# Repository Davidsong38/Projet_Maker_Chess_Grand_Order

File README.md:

# Projet-Maker--chiquier
Projet d'échiquier électronique

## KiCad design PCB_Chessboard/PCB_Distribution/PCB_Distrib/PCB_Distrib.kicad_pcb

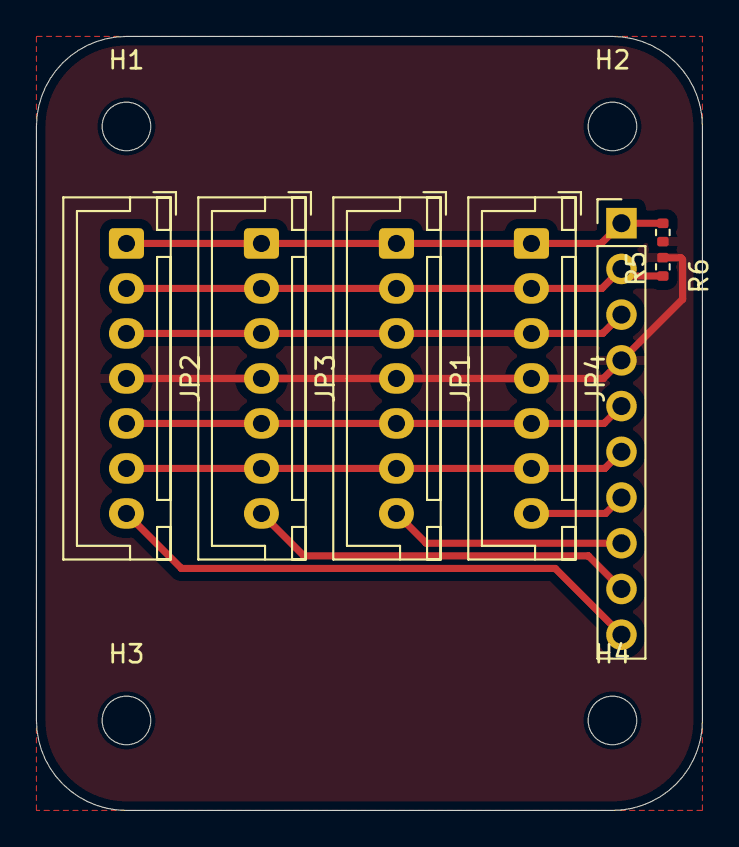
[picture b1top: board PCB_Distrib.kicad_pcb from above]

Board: 2 copper layers, 37.0 x 43.0 mm, 11 parts (0 on the bottom side), 10 nets.

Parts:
H1, H2, H3, H4: MountingHole_Pad; MountingHole_2.7mm
JP1, JP2, JP3, JP4: Conn_01x07_Socket; JST_XH_B7B-XH-A_1x07_P2.50mm_Vertical
JRasp1: Conn_01x10_Socket; PinHeader_1x10_P2.54mm_Vertical
R5, R6: 4.7k; R_0402_1005Metric

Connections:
+3.3V: JP1.4, JP2.4, JP3.4, JP4.4, JRasp1.4, R5.1, R6.1
+5V: JP1.5, JP2.5, JP3.5, JP4.5, JRasp1.5
GND: JP1.3, JP2.3, JP3.3, JP4.3, JRasp1.3
GPIO04: JP2.7, JRasp1.10
GPIO17: JP1.7, JRasp1.8
GPIO22: JP4.7, JRasp1.7
GPIO27: JP3.7, JRasp1.9
LED.DIN: JP1.6, JP2.6, JP3.6, JP4.6, JRasp1.6
SCL: JP1.2, JP2.2, JP3.2, JP4.2, JRasp1.2, R6.2
SDA: JP1.1, JP2.1, JP3.1, JP4.1, JRasp1.1, R5.2

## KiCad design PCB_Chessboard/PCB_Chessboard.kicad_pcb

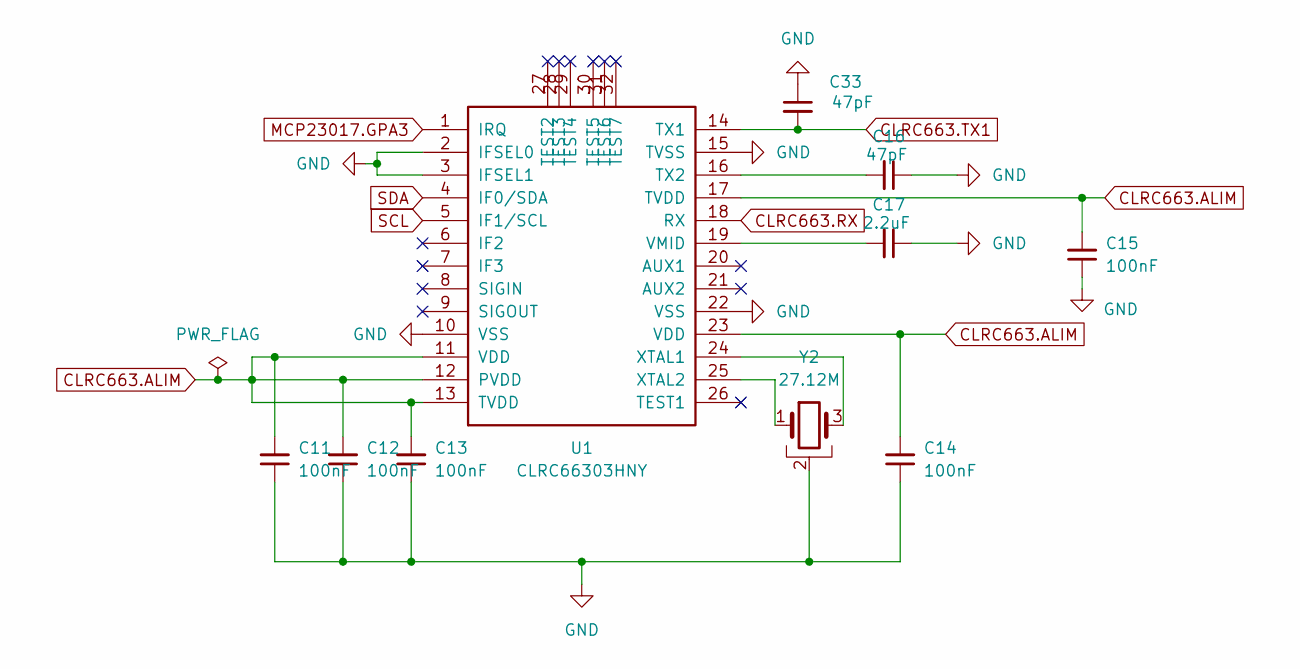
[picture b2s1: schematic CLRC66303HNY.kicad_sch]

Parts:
C11, C12, C13, C14, C15: 100nF; C_0402_1005Metric
C16, C33: 47pF; C_0402_1005Metric
C17: 2.2uF; C_0402_1005Metric
U1: CLRC66303HNY; HVQFN-32-1EP_5x5mm_P0.5mm_EP3.1x3.1mm
Y2: 27.12M; Crystal_SMD_2016-4Pin_2.0x1.6mm

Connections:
CLRC663.ALIM: C11.2, C12.2, C13.2, C14.2, C15.2, U1.11 (VDD), U1.12 (PVDD), U1.13 (TVDD), U1.17 (TVDD), U1.23 (VDD); also elsewhere on the board
CLRC663.RX: U1.18 (RX); also elsewhere on the board
CLRC663.TX1: C33.2, U1.14 (TX1); also elsewhere on the board
GND: C11.1, C12.1, C13.1, C14.1, C15.1, C16.1, C17.1, C33.1, U1.2 (IFSEL0), U1.3 (IFSEL1), U1.10 (VSS), U1.15 (TVSS), U1.22 (VSS), Y2.2; also elsewhere on the board
MCP23017.GPA3: U1.1 (IRQ); also elsewhere on the board
unnamed: C16.2, U1.16 (TX2)
unnamed: C17.2, U1.19 (VMID)
unnamed: U1.24 (XTAL1), Y2.3
unnamed: U1.25 (XTAL2), Y2.1
SCL: U1.5 (IF1/SCL); also elsewhere on the board
SDA: U1.4 (IF0/SDA); also elsewhere on the board

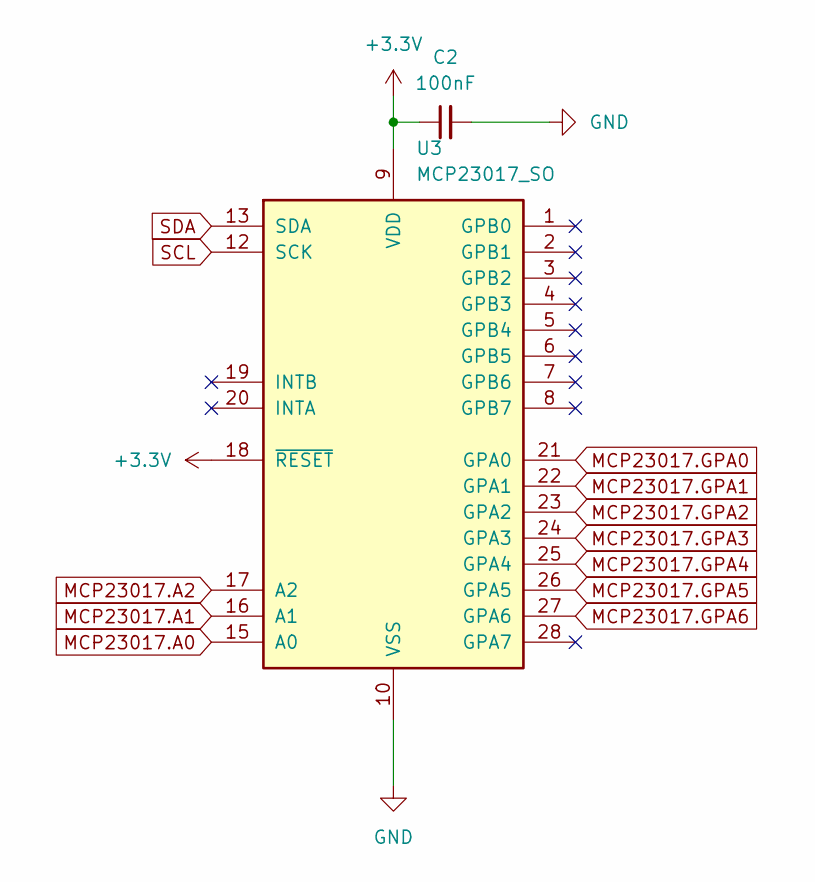
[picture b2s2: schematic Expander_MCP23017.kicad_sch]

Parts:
C2: 100nF; C_0402_1005Metric
U3: MCP23017_SO; SOIC-28W_7.5x17.9mm_P1.27mm

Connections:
+3.3V: C2.1, U3.9 (VDD), U3.18 (~RESET); also elsewhere on the board
GND: C2.2, U3.10 (VSS); also elsewhere on the board
MCP23017.A0: U3.15 (A0); also elsewhere on the board
MCP23017.A1: U3.16 (A1); also elsewhere on the board
MCP23017.A2: U3.17 (A2); also elsewhere on the board
MCP23017.GPA0: U3.21 (GPA0); also elsewhere on the board
MCP23017.GPA1: U3.22 (GPA1); also elsewhere on the board
MCP23017.GPA2: U3.23 (GPA2); also elsewhere on the board
MCP23017.GPA3: U3.24 (GPA3); also elsewhere on the board
MCP23017.GPA4: U3.25 (GPA4); also elsewhere on the board
MCP23017.GPA5: U3.26 (GPA5); also elsewhere on the board
MCP23017.GPA6: U3.27 (GPA6); also elsewhere on the board
SCL: U3.12 (SCK); also elsewhere on the board
SDA: U3.13 (SDA); also elsewhere on the board

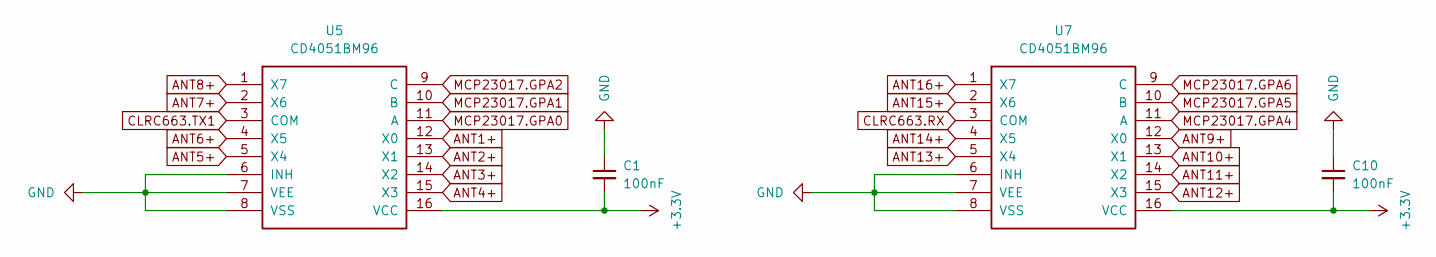
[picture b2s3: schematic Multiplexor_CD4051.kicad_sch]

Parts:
C1, C10: 100nF; C_0402_1005Metric
U5, U7: CD4051BM96; SOIC-16_3.9x9.9mm_P1.27mm

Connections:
+3.3V: C1.2, C10.2, U5.16 (VCC), U7.16 (VCC); also elsewhere on the board
ANT1+: U5.12 (X0); also elsewhere on the board
ANT2+: U5.13 (X1); also elsewhere on the board
ANT3+: U5.14 (X2); also elsewhere on the board
ANT4+: U5.15 (X3); also elsewhere on the board
ANT5+: U5.5 (X4); also elsewhere on the board
ANT6+: U5.4 (X5); also elsewhere on the board
ANT7+: U5.2 (X6); also elsewhere on the board
ANT8+: U5.1 (X7); also elsewhere on the board
ANT9+: U7.12 (X0); also elsewhere on the board
ANT10+: U7.13 (X1); also elsewhere on the board
ANT11+: U7.14 (X2); also elsewhere on the board
ANT12+: U7.15 (X3); also elsewhere on the board
ANT13+: U7.5 (X4); also elsewhere on the board
ANT14+: U7.4 (X5); also elsewhere on the board
ANT15+: U7.2 (X6); also elsewhere on the board
ANT16+: U7.1 (X7); also elsewhere on the board
CLRC663.RX: U7.3 (COM); also elsewhere on the board
CLRC663.TX1: U5.3 (COM); also elsewhere on the board
GND: C1.1, C10.1, U5.6 (INH), U5.7 (VEE), U5.8 (VSS), U7.6 (INH), U7.7 (VEE), U7.8 (VSS); also elsewhere on the board
MCP23017.GPA0: U5.11 (A); also elsewhere on the board
MCP23017.GPA1: U5.10 (B); also elsewhere on the board
MCP23017.GPA2: U5.9 (C); also elsewhere on the board
MCP23017.GPA4: U7.11 (A); also elsewhere on the board
MCP23017.GPA5: U7.10 (B); also elsewhere on the board
MCP23017.GPA6: U7.9 (C); also elsewhere on the board

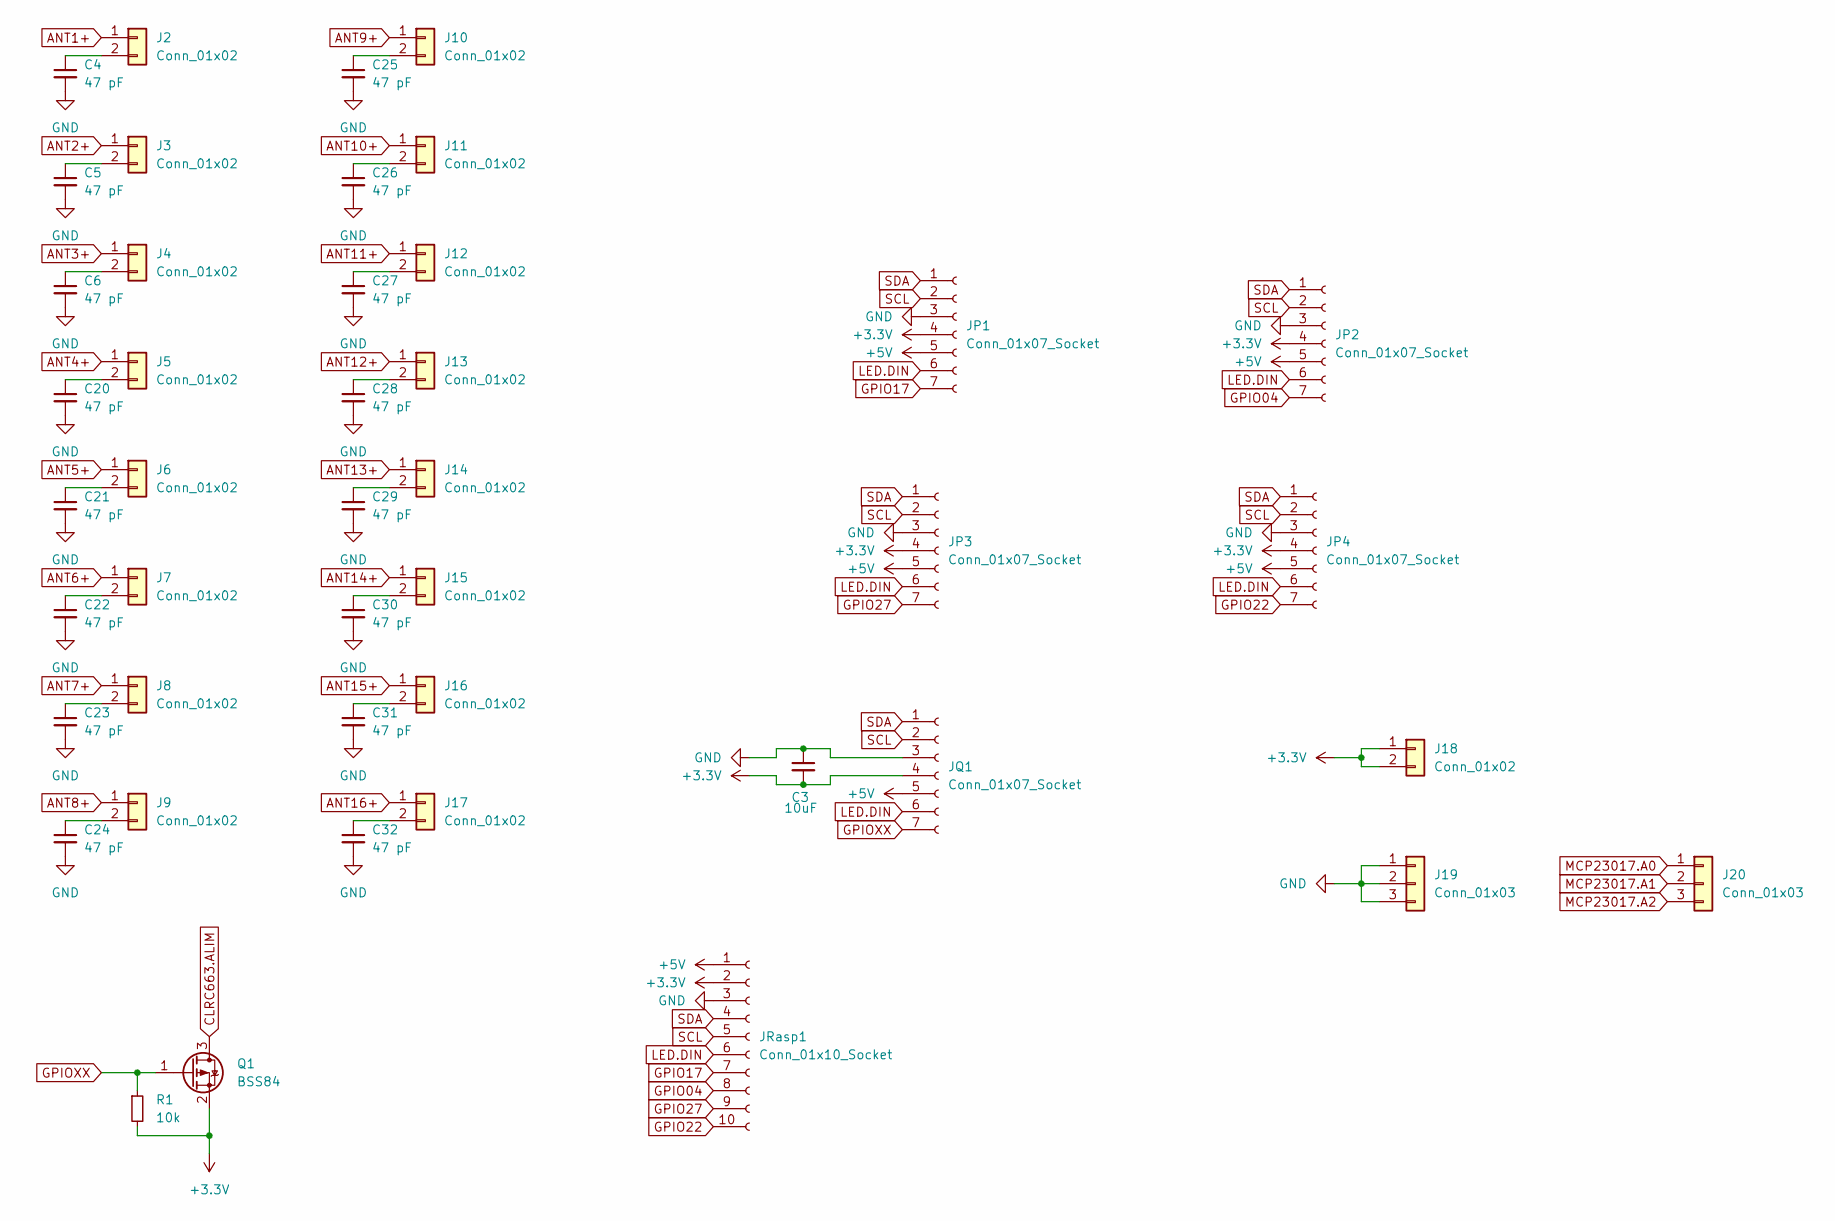
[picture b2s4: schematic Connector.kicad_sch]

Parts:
C3: 10uF; C_0402_1005Metric
C4, C5, C6, C20, C21, C22, C23, C24, C25, C26, C27, C28, C29, C30, C31, C32: 47 pF; C_0402_1005Metric
J2, J3, J4, J5, J6, J7, J8, J9, J10, J11, J12, J13, J14, J15, J16, J17, J18: Conn_01x02; PinHeader_1x02_P2.54mm_Vertical
J19, J20: Conn_01x03; PinHeader_1x03_P2.54mm_Vertical
JP1, JP2, JP3, JP4: Conn_01x07_Socket; JST_VH_B7PS-VH_1x07_P3.96mm_Horizontal
JQ1: Conn_01x07_Socket; JST_VH_B7PS-VH_1x07_P3.96mm_Horizontal
JRasp1: Conn_01x10_Socket; PinHeader_1x10_P1.00mm_Vertical
Q1: BSS84; SOT-23
R1: 10k; R_0402_1005Metric

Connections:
+3.3V: C3.2, J18.1, J18.2, JP1.4, JP2.4, JP3.4, JP4.4, JQ1.4, JRasp1.2, Q1.2 (S), R1.2; also elsewhere on the board
+5V: JP1.5, JP2.5, JP3.5, JP4.5, JQ1.5, JRasp1.1; also elsewhere on the board
ANT1+: J2.1; also elsewhere on the board
ANT2+: J3.1; also elsewhere on the board
ANT3+: J4.1; also elsewhere on the board
ANT4+: J5.1; also elsewhere on the board
ANT5+: J6.1; also elsewhere on the board
ANT6+: J7.1; also elsewhere on the board
ANT7+: J8.1; also elsewhere on the board
ANT8+: J9.1; also elsewhere on the board
ANT9+: J10.1; also elsewhere on the board
ANT10+: J11.1; also elsewhere on the board
ANT11+: J12.1; also elsewhere on the board
ANT12+: J13.1; also elsewhere on the board
ANT13+: J14.1; also elsewhere on the board
ANT14+: J15.1; also elsewhere on the board
ANT15+: J16.1; also elsewhere on the board
ANT16+: J17.1; also elsewhere on the board
CLRC663.ALIM: Q1.3 (D); also elsewhere on the board
GND: C3.1, C4.2, C5.2, C6.2, C20.2, C21.2, C22.2, C23.2, C24.2, C25.2, C26.2, C27.2, C28.2, C29.2, C30.2, C31.2, C32.2, J19.1, J19.2, J19.3, JP1.3, JP2.3, JP3.3, JP4.3, JQ1.3, JRasp1.3; also elsewhere on the board
GPIOXX: JQ1.7, Q1.1 (G), R1.1
LED.DIN: JP1.6, JP2.6, JP3.6, JP4.6, JQ1.6, JRasp1.6; also elsewhere on the board
MCP23017.A0: J20.1; also elsewhere on the board
MCP23017.A1: J20.2; also elsewhere on the board
MCP23017.A2: J20.3; also elsewhere on the board
unnamed: C4.1, J2.2
unnamed: C5.1, J3.2
unnamed: C6.1, J4.2
unnamed: C20.1, J5.2
unnamed: C21.1, J6.2
unnamed: C22.1, J7.2
unnamed: C23.1, J8.2
unnamed: C24.1, J9.2
unnamed: C25.1, J10.2
unnamed: C26.1, J11.2
unnamed: C27.1, J12.2
unnamed: C28.1, J13.2
unnamed: C29.1, J14.2
unnamed: C30.1, J15.2
unnamed: C31.1, J16.2
unnamed: C32.1, J17.2
unnamed: JP1.7, JRasp1.7
unnamed: JP2.7, JRasp1.8
unnamed: JP3.7, JRasp1.9
unnamed: JP4.7, JRasp1.10
SCL: JP1.2, JP2.2, JP3.2, JP4.2, JQ1.2, JRasp1.5; also elsewhere on the board
SDA: JP1.1, JP2.1, JP3.1, JP4.1, JQ1.1, JRasp1.4; also elsewhere on the board

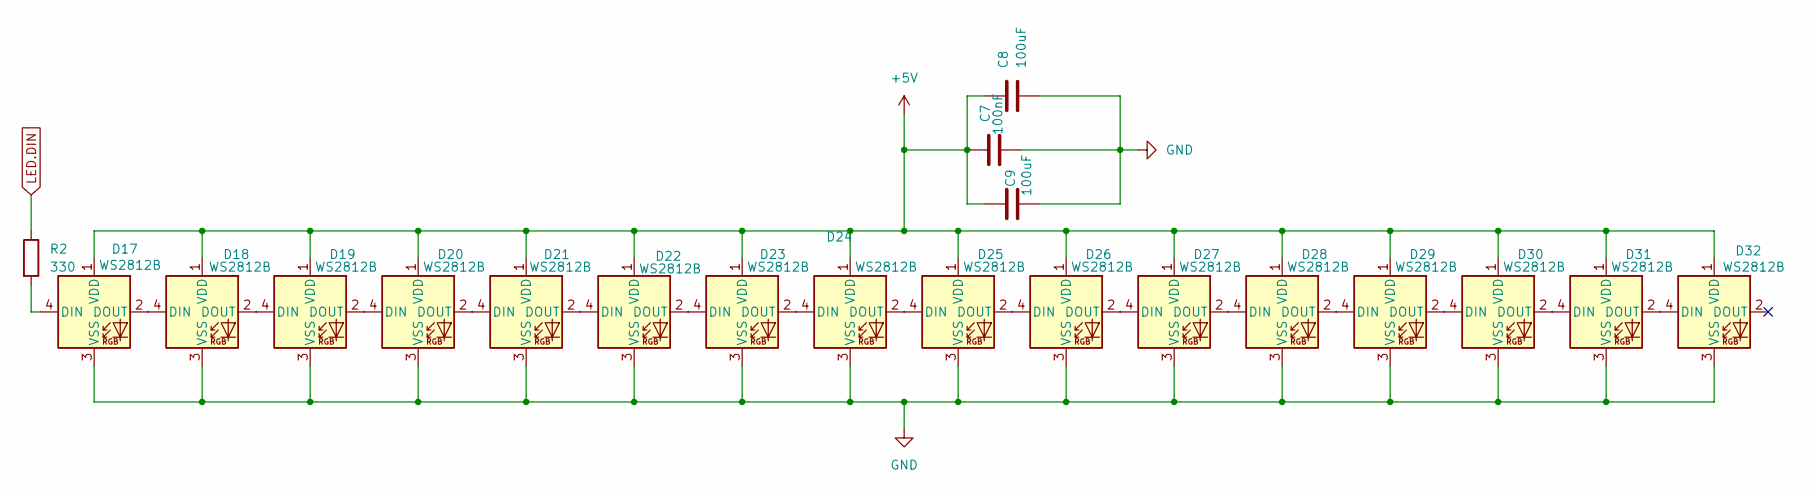
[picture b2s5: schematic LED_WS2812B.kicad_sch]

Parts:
C7: 100nF; C_0402_1005Metric
C8, C9: 100uF; C_0402_1005Metric
D17, D18, D19, D20, D21, D22, D23, D24, D25, D26, D27, D28, D29, D30, D31, D32: WS2812B; LED_WS2812B_PLCC4_5.0x5.0mm_P3.2mm
R2: 330; R_0402_1005Metric

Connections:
+5V: C7.1, C8.1, C9.1, D17.1 (VDD), D18.1 (VDD), D19.1 (VDD), D20.1 (VDD), D21.1 (VDD), D22.1 (VDD), D23.1 (VDD), D24.1 (VDD), D25.1 (VDD), D26.1 (VDD), D27.1 (VDD), D28.1 (VDD), D29.1 (VDD), D30.1 (VDD), D31.1 (VDD), D32.1 (VDD); also elsewhere on the board
GND: C7.2, C8.2, C9.2, D17.3 (VSS), D18.3 (VSS), D19.3 (VSS), D20.3 (VSS), D21.3 (VSS), D22.3 (VSS), D23.3 (VSS), D24.3 (VSS), D25.3 (VSS), D26.3 (VSS), D27.3 (VSS), D28.3 (VSS), D29.3 (VSS), D30.3 (VSS), D31.3 (VSS), D32.3 (VSS); also elsewhere on the board
LED.DIN: R2.1; also elsewhere on the board
unnamed: D17.4 (DIN), R2.2
unnamed: D17.2 (DOUT), D18.4 (DIN)
unnamed: D18.2 (DOUT), D19.4 (DIN)
unnamed: D19.2 (DOUT), D20.4 (DIN)
unnamed: D20.2 (DOUT), D21.4 (DIN)
unnamed: D21.2 (DOUT), D22.4 (DIN)
unnamed: D22.2 (DOUT), D23.4 (DIN)
unnamed: D23.2 (DOUT), D24.4 (DIN)
unnamed: D24.2 (DOUT), D25.4 (DIN)
unnamed: D25.2 (DOUT), D26.4 (DIN)
unnamed: D26.2 (DOUT), D27.4 (DIN)
unnamed: D27.2 (DOUT), D28.4 (DIN)
unnamed: D28.2 (DOUT), D29.4 (DIN)
unnamed: D29.2 (DOUT), D30.4 (DIN)
unnamed: D30.2 (DOUT), D31.4 (DIN)
unnamed: D31.2 (DOUT), D32.4 (DIN)

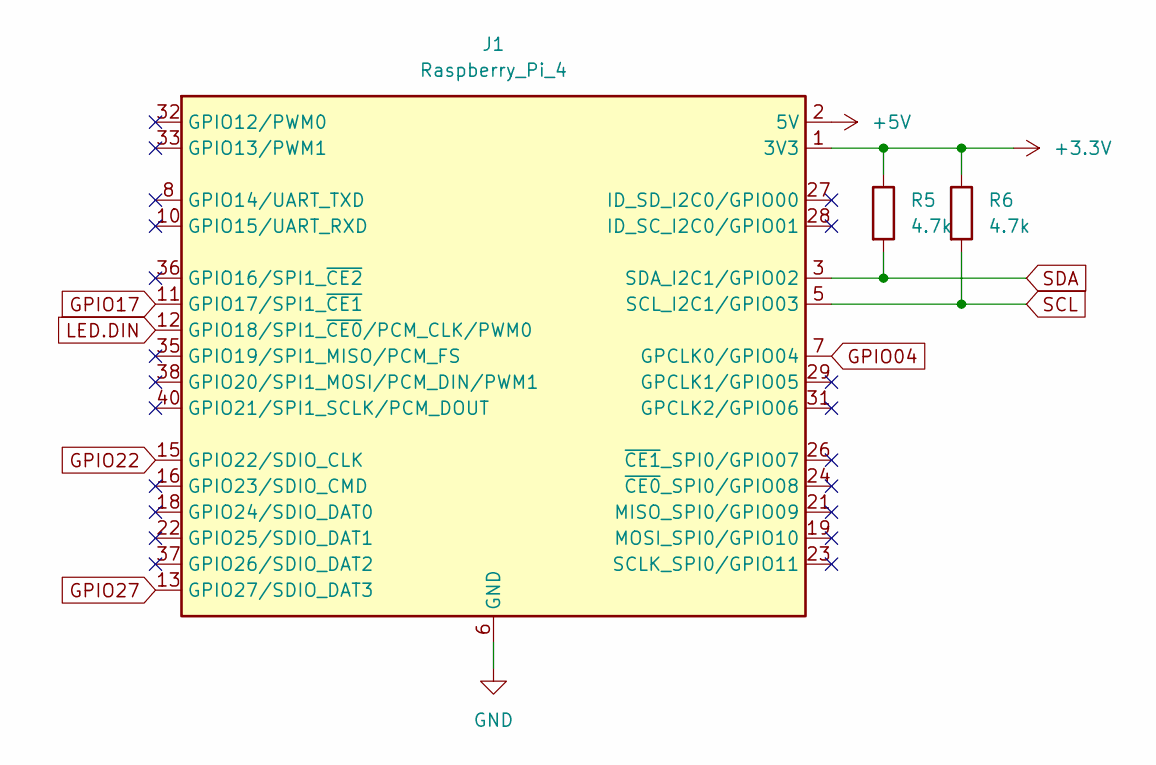
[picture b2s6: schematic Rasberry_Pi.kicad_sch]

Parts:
J1: Raspberry_Pi_4
R5, R6: 4.7k; R_0402_1005Metric

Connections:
unnamed: J1.1 (3V3), J1.17 (3V3), R5.1, R6.1
unnamed: J1.2 (5V), J1.4 (5V)
unnamed: J1.3 (SDA_I2C1/GPIO02), R5.2
unnamed: J1.5 (SCL_I2C1/GPIO03), R6.2
unnamed: J1.6 (GND), J1.9 (GND), J1.14 (GND), J1.20 (GND), J1.25 (GND), J1.30 (GND), J1.34 (GND), J1.39 (GND)

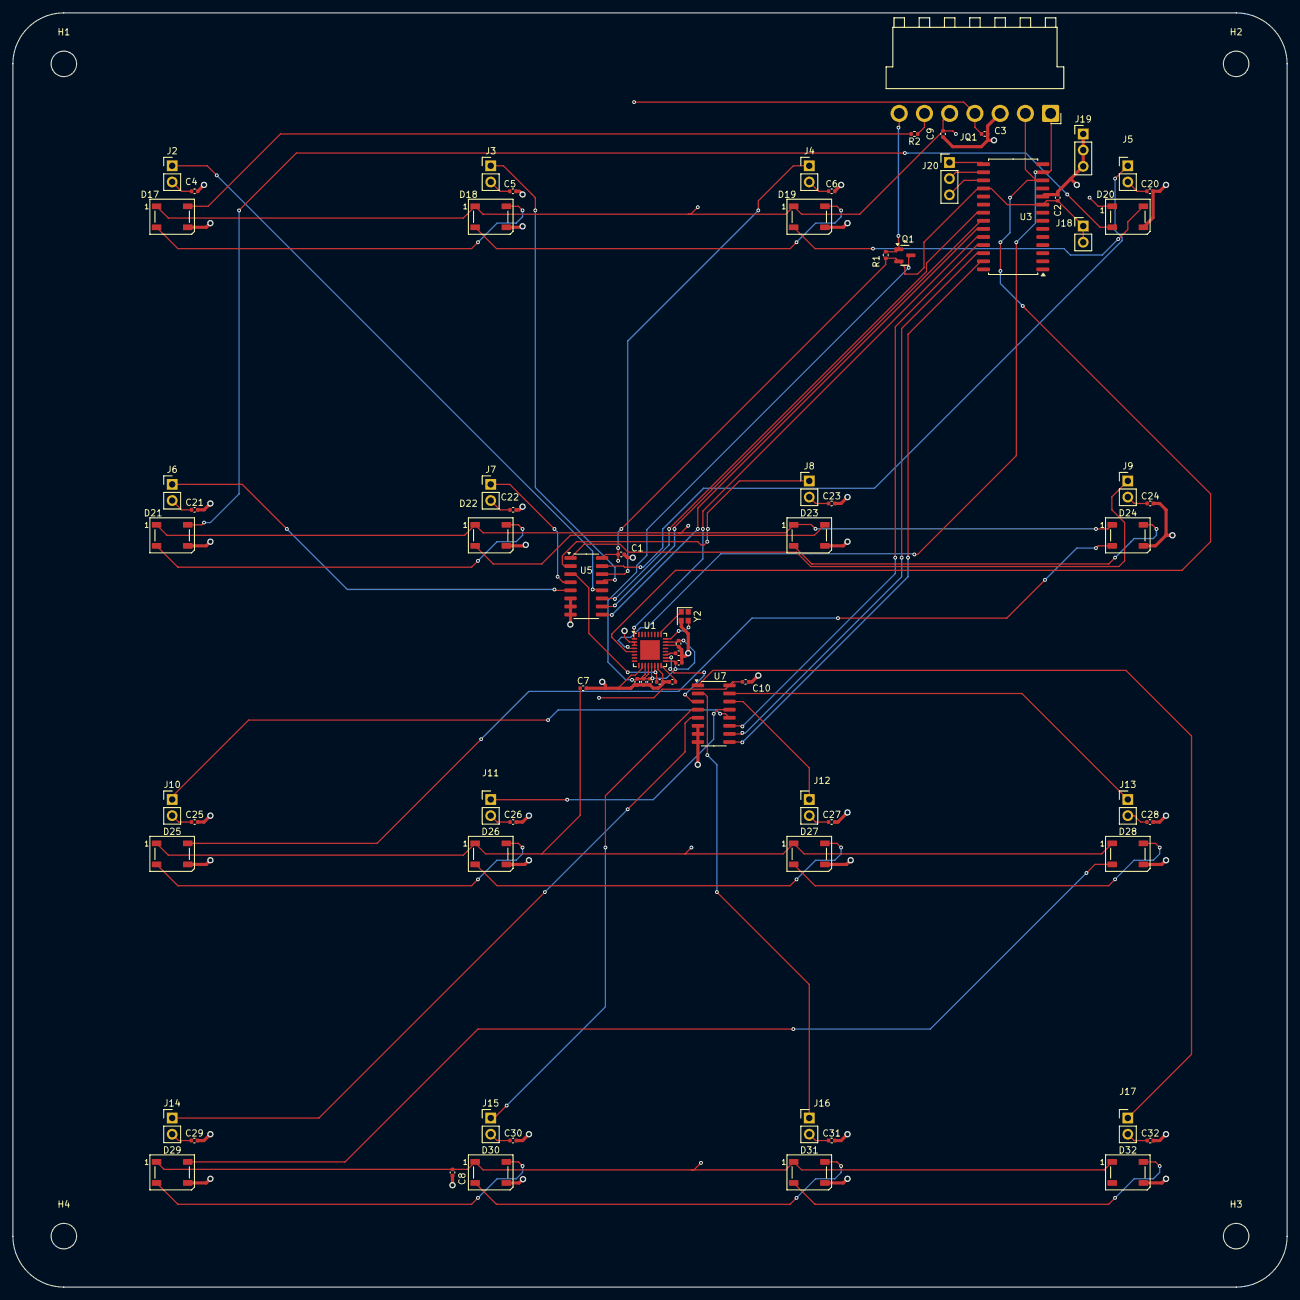
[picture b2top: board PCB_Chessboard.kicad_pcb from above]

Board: 4 copper layers, 200.0 x 200.0 mm, 79 parts (0 on the bottom side), 72 nets.

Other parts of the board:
H1, H2, H3, H4: MountingHole; MountingHole_4mm

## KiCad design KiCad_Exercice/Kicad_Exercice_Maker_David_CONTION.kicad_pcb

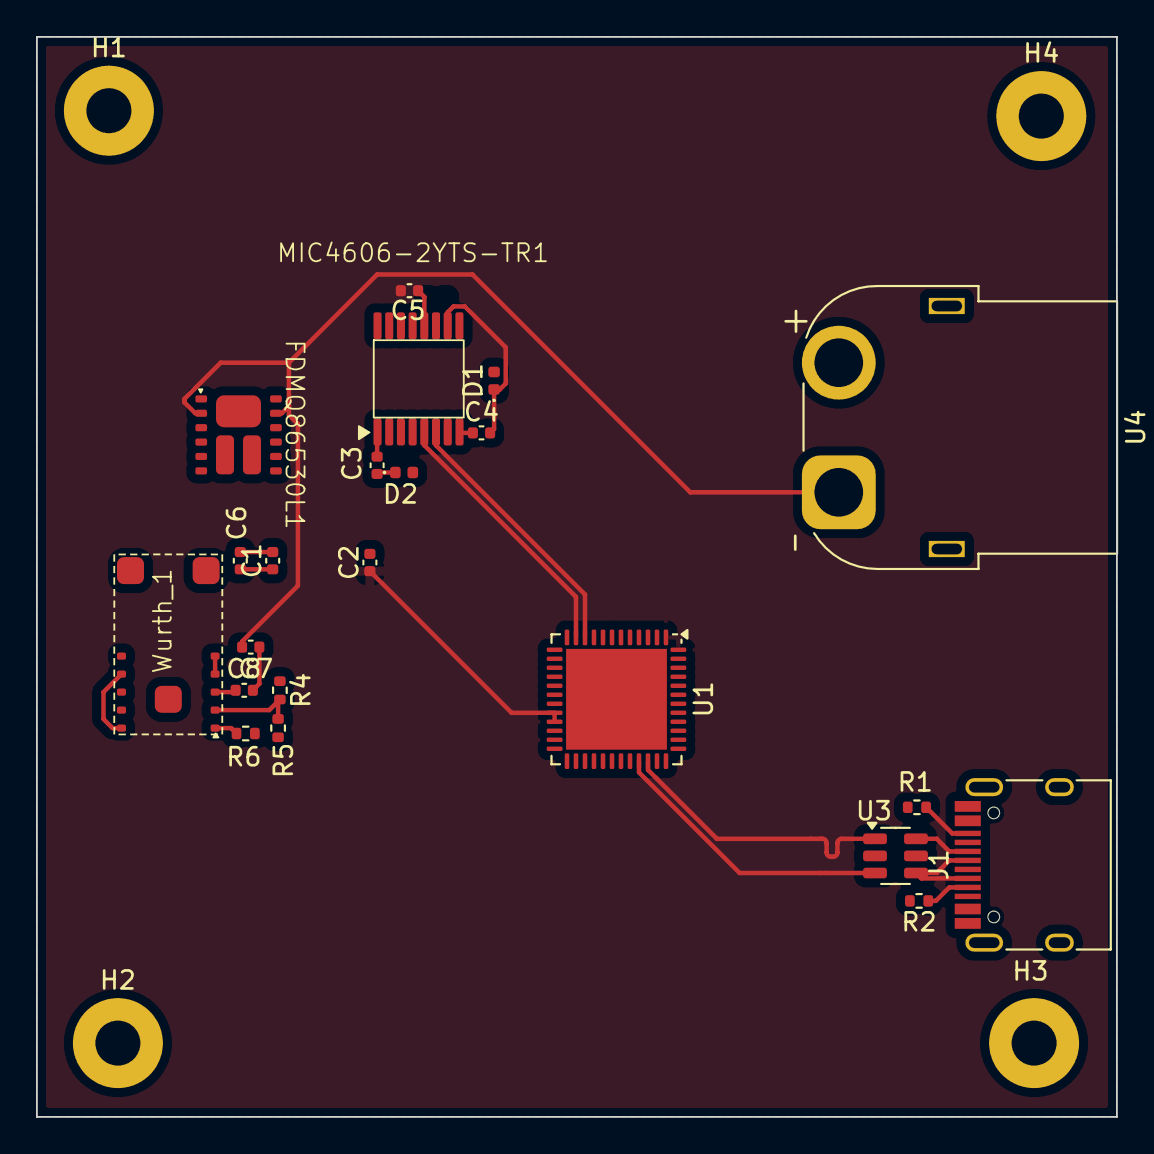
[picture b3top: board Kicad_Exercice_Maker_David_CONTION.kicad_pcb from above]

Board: 4 copper layers, 60.0 x 60.0 mm, 26 parts (0 on the bottom side), 27 nets.

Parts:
C1: 4.7u; C_0402_1005Metric
C2, C8: 1u; C_0402_1005Metric
C3, C4, C5: 20n; C_0402_1005Metric
C6: 47u; C_0402_1005Metric
C7: 10u; C_0402_1005Metric
D1, D2: D_Zener; D_0402_1005Metric
FDMQ86530L1: FDMQ86530L
H1, H2, H3, H4: MountingHole_Pad; MountingHole_2.5mm_Pad
J1: USB_C_Receptacle_USB2.0_16P; USB_C_Receptacle_HRO_TYPE-C-31-M-12
MIC4606-2YTS-TR1: MIC_4606
R1, R2: 5.1k; R_0402_1005Metric
R4: 402k; R_0402_1005Metric
R5: 80.6k; R_0402_1005Metric
R6: 5.6k; R_0402_1005Metric
U1: STM32G431CBUx; QFN-48-1EP_7x7mm_P0.5mm_EP5.6x5.6mm
U3: USBLC6-2SC6; SOT-23-6
U4: AMASS_XT60PW-F_1x02_P7.20mm_Horizontal
Wurth_1: 171013801

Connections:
AHI: MIC4606-2YTS-TR1.6 (AHI), U1.10 (PA2)
AHO: FDMQ86530L1.12 (G4), MIC4606-2YTS-TR1.9 (AHO)
AHS: C4.2, D1.1 (K), FDMQ86530L1.10 (D3/S4), MIC4606-2YTS-TR1.10 (AHS)
ALI: MIC4606-2YTS-TR1.5 (ALI), U1.11 (PA3)
ALO: FDMQ86530L1.9 (G3), MIC4606-2YTS-TR1.11 (ALO)
BHI: MIC4606-2YTS-TR1.3 (BHI), U1.8 (PA0)
BHO: FDMQ86530L1.1 (G1), MIC4606-2YTS-TR1.16 (BHO)
BHS: C3.2, D2.1 (K), FDMQ86530L1.3 (S1/D2), MIC4606-2YTS-TR1.15 (BHS)
BLI: MIC4606-2YTS-TR1.4 (BLI), U1.9 (PA1)
BLO: FDMQ86530L1.4 (G2), MIC4606-2YTS-TR1.14 (BLO)
GND: C1.2, C2.2, C5.2, C6.2, C7.2, C8.2, D1.2 (A), D2.2 (A), H1.1, H2.1, H3.1, H4.1, J1.A1 (GND), J1.A12 (GND), J1.B1 (GND), J1.B12 (GND), J1.S1 (SHIELD), R1.2, R2.2, R5.2, R6.2, U1.49 (VSS), U3.2 (GND), U4.2 (V-), Wurth_1.10 (AGND), Wurth_1.13 (PGND)
unnamed: J1.A5 (CC1), R2.1
unnamed: J1.B5 (CC2), R1.1
unnamed: J1.A6 (D+), J1.B6 (D+), U3.6 (I/O1)
unnamed: J1.A7 (D-), J1.B7 (D-), U3.4 (I/O2)
unnamed: C4.1, MIC4606-2YTS-TR1.8 (AHB)
unnamed: C3.1, MIC4606-2YTS-TR1.1 (BHB)
unnamed: J1.A4 (VBUS), J1.A9 (VBUS), J1.B4 (VBUS), J1.B9 (VBUS), U3.5 (VBUS)
unnamed: Wurth_1.9 (VIN), Wurth_1.12 (EN)
unnamed: R4.2, R5.1, Wurth_1.2 (FB)
unnamed: R6.1, Wurth_1.1 (FSW)
unnamed: C8.1, Wurth_1.3 (VCC)
USB_DM: U1.33 (PA11), U3.3 (I/O2)
USB_DP: U1.34 (PA12), U3.1 (I/O1)
VDD: C1.1, C5.1, C6.1, MIC4606-2YTS-TR1.12 (VDD), R4.1
VIN: C7.1, FDMQ86530L1.2 (D1/D4), FDMQ86530L1.11 (D1/D4), U4.1 (V+)
VuC: C2.1, U1.1 (VBAT), U1.20 (VREF+), U1.21 (VDDA), U1.23 (VDD), U1.35 (VDD), U1.48 (VDD)

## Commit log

2025-02-04 LE commit
2025-02-04 c la bonne
2025-02-04 little correction
2025-02-04 Game State Fusion
2025-02-06 Grosse maj de la mort qui tue
2025-02-06 Piece is moving and killing !!!
2025-02-06 debug knight
2025-02-07 jeux d'echec fonctionnel + roque en développement
2025-02-07 Roque implemented
2025-02-08 Roque Debug
2025-02-10 debug roque
2025-02-10 en passant rules dev
2025-02-10 en passant rule impemented
2025-02-11 pawn become queen at the end of board
2025-02-11 mixing effect debut
2025-02-11 debug
2025-02-12 shuffle for select target on effect
2025-02-13 Effect game system
2025-02-14 Debug Trigger Effect
2025-02-15 Medusa_Saber finished
2025-02-15 implementing characters effect
2025-02-15 Kiara programming
2025-02-16 Kiara debugging
2025-02-17 BIG debugging Kiara
2025-02-17 kiara and ushi finished!!!
2025-02-17 gitignore update
2025-02-18 arcueid coding debut
2025-02-18 Arceuid done
2025-02-19 artoria coding
2025-02-19 Artoria done
2025-02-19 petit réglage
2025-02-19 commit avant que l'échiquier soit cassé
2025-02-20 Merlin,Okita implemented Xu_Fu developping
2025-02-21 petite correction EffectHandler
2025-02-22 Xu Fu done, making Nitocris Alter, issue respawn piece
2025-02-23 Nitocris done and Gilgamesh is SELFISH
2025-02-23 Gilgamesh not selfish anymore
2025-02-23 BIG BUTTON AND COLOR LOG
2025-02-24 Cleaning !!!
2025-02-24 Selection state and cleaning
2025-02-25 Effect system rework, selection multiple target and cleaning
2025-02-25 new phase context and big cleaning
2025-02-26 Event added and cleaning
2025-02-27 move and effectRange pattern added
2025-02-28 A lot of getter for EVENT && GameEngine cleaning
2025-03-01 debugging
2025-03-01 kiara repaired
2025-03-02 all character repaired
2025-03-03 coding characters and corrections
2025-03-03 kukulkan finished
2025-03-04 changes effect range et tamamo dev
2025-03-04 new system effect range complete
2025-03-04 correction tamamo complete
2025-03-24 Create PCB_Chessboard
2025-03-24 PCB quadrant
2025-03-24 PCB quadrant with mounting Hole
2025-03-24 PCB distribution done
2025-03-24 update pcb
2025-03-24 PCB quadrant finalisé
2025-03-27 Fixing tamamo
2025-03-31 I2C start
2025-04-03 I2C dev
2025-04-27 add couture
2025-04-27 add useless box
2025-04-27 JST 3 Pin
